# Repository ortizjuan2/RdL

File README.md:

# RdL
RdL project files
Used to design RdL main circuit board
and firmware software

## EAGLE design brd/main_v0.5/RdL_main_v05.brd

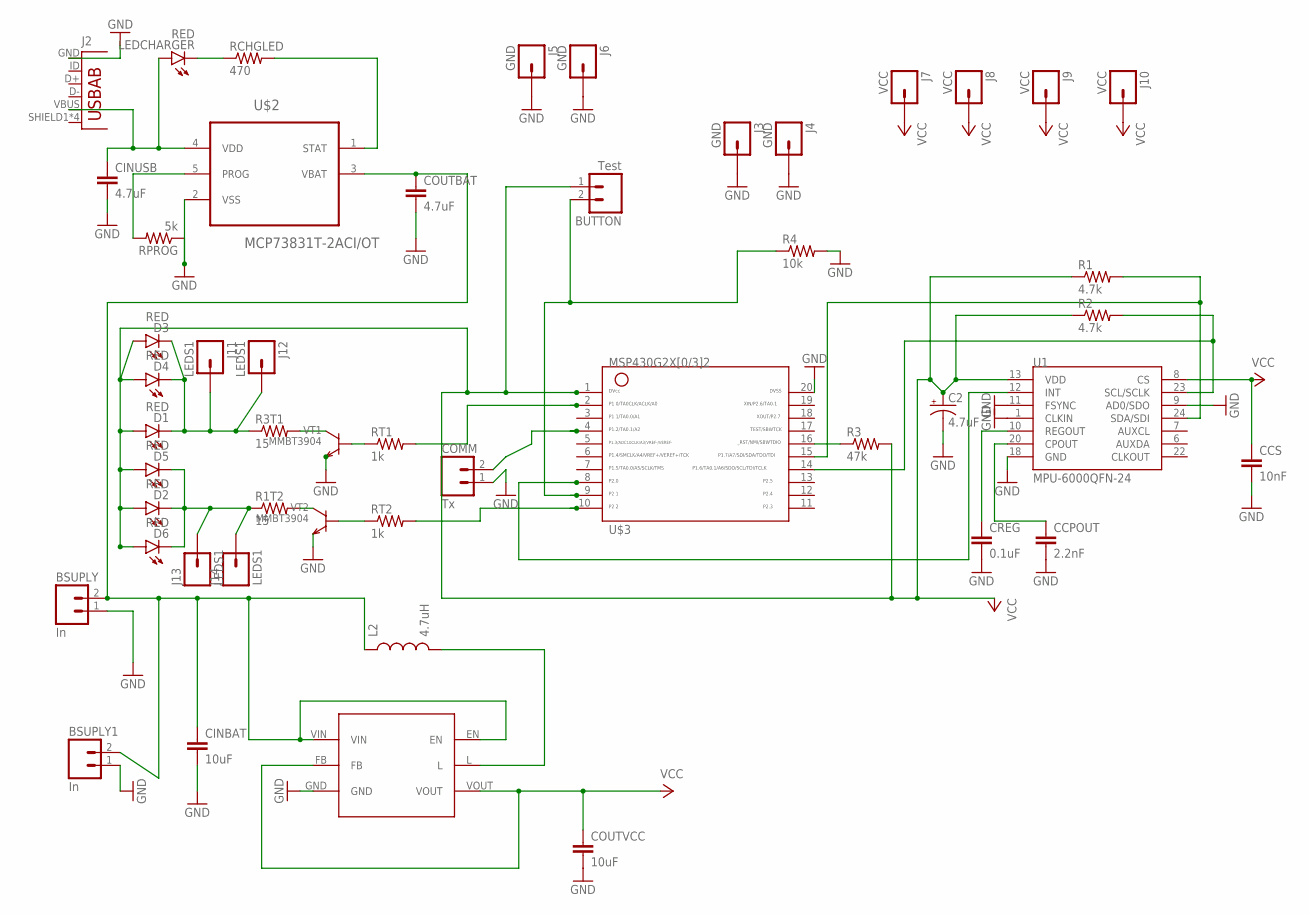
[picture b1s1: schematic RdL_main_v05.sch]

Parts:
BSUPLY, BSUPLY1: In; 1X02
BUTTON: Test; 1X02
C2: 4.7uF; EIA3216
CCPOUT: 2.2nF; 0805
CCS: 10nF; 0805
CINBAT: 10uF; 0805
CINUSB: 4.7uF; 0805
COMM: Tx; 1X02
COUTBAT: 4.7uF; 0805
COUTVCC: 10uF; 0805
CREG: 0.1uF; 0805
D1, D2, D3, D4, D5, D6: RED; LED-1206
J2: USB-AB; USB-AB-MICRO-SMD
J3, J4, J5, J6: GND; 1X01
J7, J8, J9, J10: VCC; 1X01
J11, J12, J13, J14: LEDS1; 1X01
L2: 4.7uH; INDUCTOR_4.7UH
LEDCHARGER: RED; LED-1206
R1, R2: 4.7k; 1206
R1T2, R3T1: 15; 1206
R3: 47k; 1206
R4: 10k; 1206
RCHGLED: 470; 1206
RPROG: 5k; 1206
RT1, RT2: 1k; 1206
U1: MPU-6000QFN-24; QFN-24-TESTING
U$1: TLV61225; TLV61225DCKT
U$2: MCP73831T-2ACI/OT; SOT95P280X145-5N
U$3: G2X[0/3]2---PW20; PW20
VT1, VT2: MMBT3904; SOT23-BEC

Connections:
GND: BSUPLY.1, BSUPLY1.1, C2.C (-), CCPOUT.2, CCS.2, CINBAT.2, CINUSB.2, COMM.1, COUTBAT.2, COUTVCC.2, CREG.2, J2.GND, J3.1, J4.1, J5.1, J6.1, R4.2, RPROG.1, U1.1 (CLKIN), U1.9 (AD0/SDO), U1.11 (FSYNC), U1.18 (GND), U$1.GND, U$2.2 (VSS), U$3.20, VT1.E, VT2.E
unnamed: BUTTON.2, R4.1, U$3.9
unnamed: L2.P$2 (2), U$1.L
unnamed: CINUSB.1, J2.VBUS, LEDCHARGER.A, U$2.4 (VDD)
unnamed: R1T2.2, VT2.C
unnamed: R3T1.2, VT1.C
unnamed: RT1.1, VT1.B
unnamed: RT2.1, VT2.B
unnamed: RT1.2, U$3.2
unnamed: RT2.2, U$3.10
unnamed: R3.1, U$3.16
unnamed: D2.C, D5.C, D6.C, J13.1, J14.1, R1T2.1
unnamed: D1.C, D3.C, D4.C, J11.1, J12.1, R3T1.1
unnamed: COMM.2, U$3.4
unnamed: LEDCHARGER.C, RCHGLED.1
unnamed: U1.12 (INT), U$3.8
unnamed: RPROG.2, U$2.5 (PROG)
unnamed: R1.2, U1.24 (SDA/SDI), U$3.15
unnamed: R2.2, U1.23 (SCL/SCLK), U$3.14
unnamed: CREG.1, U1.10 (REGOUT)
unnamed: CCPOUT.1, U1.20 (CPOUT)
VCC: BUTTON.1, C2.A (+), CCS.1, COUTVCC.1, D1.A, D2.A, D3.A, D4.A, D5.A, D6.A, J7.1, J8.1, J9.1, J10.1, R1.1, R2.1, R3.2, U1.8 (CS), U1.13 (VDD), U$1.FB, U$1.VOUT, U$3.1
VINUSB: RCHGLED.2, U$2.1 (STAT)
VOUTBATT: BSUPLY.2, BSUPLY1.2, CINBAT.1, COUTBAT.1, L2.P$1 (1), U$1.EN, U$1.VIN, U$2.3 (VBAT)

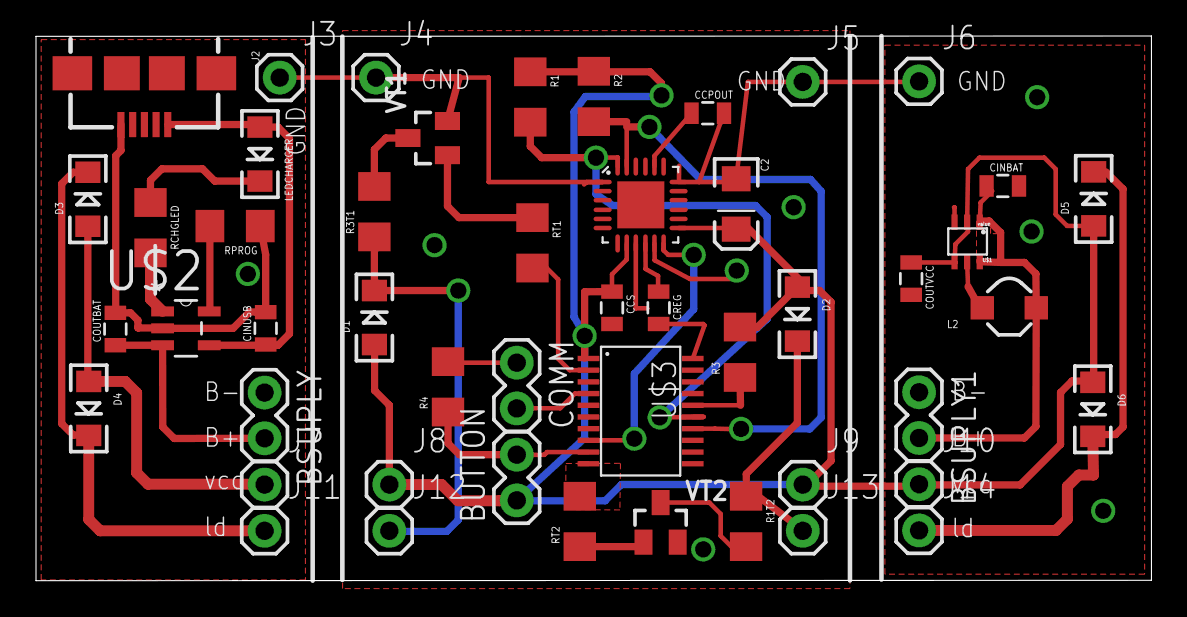
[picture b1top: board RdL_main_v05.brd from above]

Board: 2 copper layers, 62.0 x 30.3 mm, 49 parts (0 on the bottom side), 24 nets.

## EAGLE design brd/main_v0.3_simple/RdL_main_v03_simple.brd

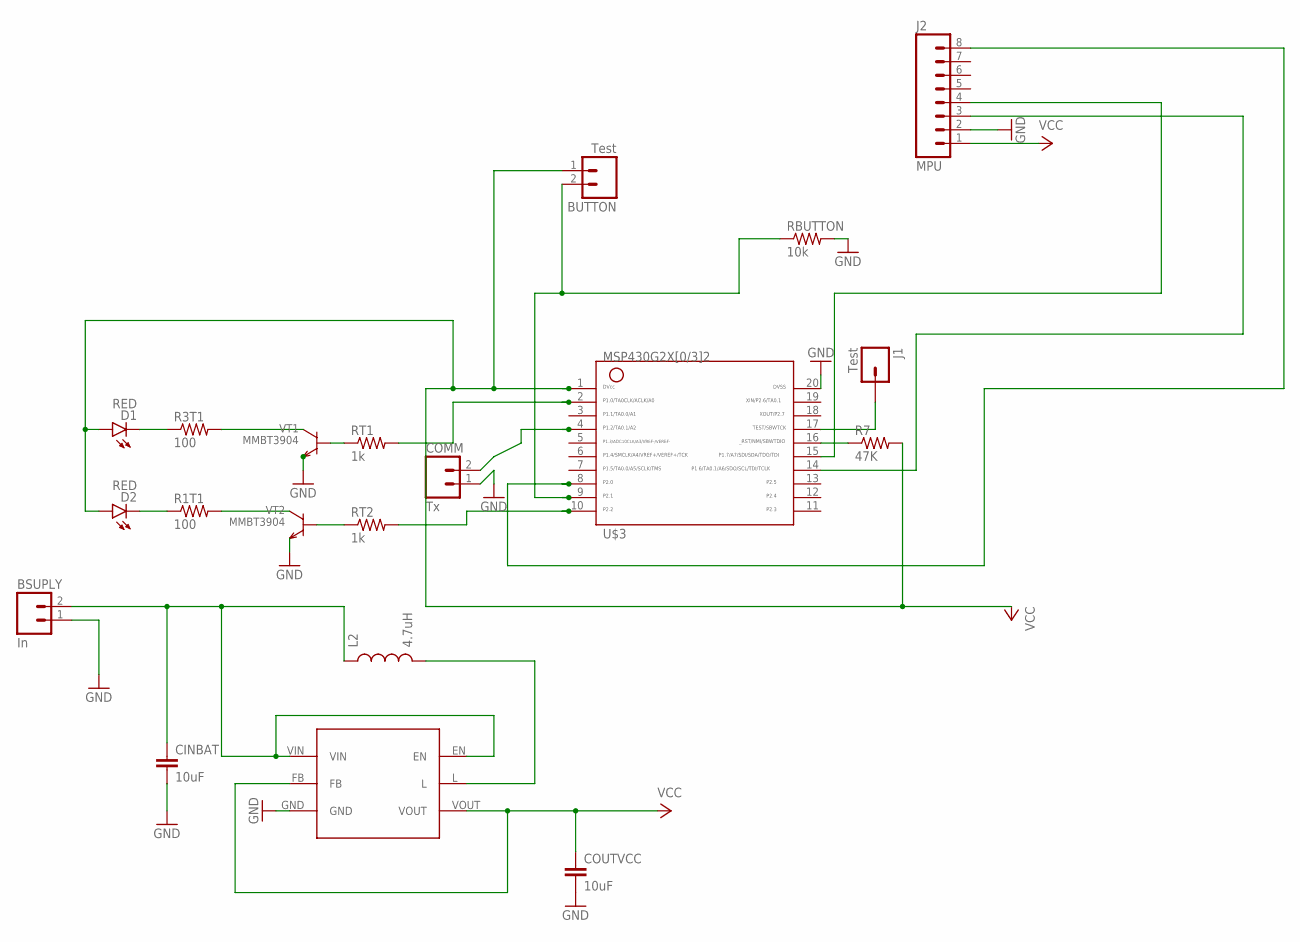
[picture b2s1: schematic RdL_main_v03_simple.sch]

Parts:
BSUPLY: In; 1X02
BUTTON: Test; 1X02
CINBAT: 10uF; 0805
COMM: Tx; 1X02
COUTVCC: 10uF; 0805
D1, D2: RED; LED-1206
J1: Test; 1X01
J2: MPU; 1X08_PIN1_NO_SILK
L2: 4.7uH; INDUCTOR_4.7UH
R1T1, R3T1: 100; 1206
R7: 47K; 0603-RES
RBUTTON: 10k; 0805
RT1, RT2: 1k; 1206
U$1: TLV61225; TLV61225DCKT
U$3: G2X[0/3]2---PW20; PW20
VT1, VT2: MMBT3904; SOT23-BEC

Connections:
GND: BSUPLY.1, CINBAT.2, COMM.1, COUTVCC.2, J2.2, RBUTTON.2, U$1.GND, U$3.20, VT1.E, VT2.E
unnamed: BUTTON.2, RBUTTON.1, U$3.9
unnamed: BSUPLY.2, CINBAT.1, L2.P$1 (1), U$1.EN, U$1.VIN
unnamed: L2.P$2 (2), U$1.L
unnamed: J1.1, U$3.17
unnamed: R1T1.2, VT2.C
unnamed: R3T1.2, VT1.C
unnamed: RT1.1, VT1.B
unnamed: RT2.1, VT2.B
unnamed: RT1.2, U$3.2
unnamed: RT2.2, U$3.10
unnamed: R7.1, U$3.16
unnamed: D2.C, R1T1.1
unnamed: D1.C, R3T1.1
unnamed: COMM.2, U$3.4
unnamed: J2.8, U$3.8
unnamed: J2.4, U$3.15
unnamed: J2.3, U$3.14
VCC: BUTTON.1, COUTVCC.1, D1.A, D2.A, J2.1, R7.2, U$1.FB, U$1.VOUT, U$3.1

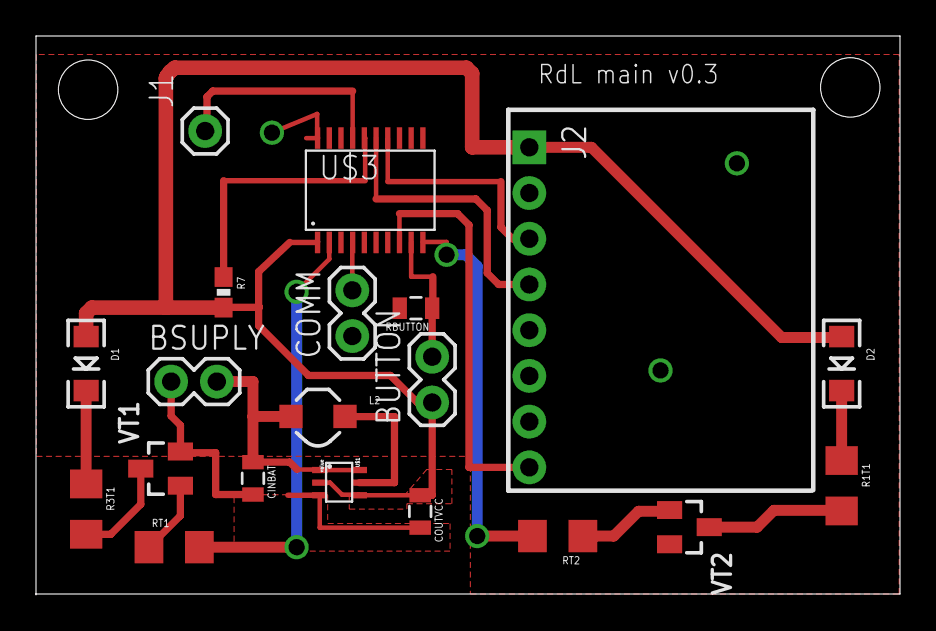
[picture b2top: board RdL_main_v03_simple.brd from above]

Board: 2 copper layers, 48.0 x 31.1 mm, 22 parts (0 on the bottom side), 19 nets.

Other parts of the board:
H1, H3: STAND-OFF

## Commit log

2016-07-17 Initial Release brd main
2016-07-17 Modified Readme file
2016-07-17 Additional first release comments
2016-07-18 Version Ready for fabrication
2016-07-18 Main board simple version 0.3 ready for production
2016-07-25 Added version 4 to divide in 3 boards
2016-07-25 Update main v4, almost ready for printing
2016-07-28 Version 4 without unrouted vias
2016-08-08 RdL version 5 ready to print

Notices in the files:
parts and their libraries:
SparkFun-Connectors: Licensing: Creative Commons ShareAlike 4.0 International - https://creativecommons.org/licenses/by-sa/4.0
